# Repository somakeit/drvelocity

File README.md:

DrVelocity
==========

A ti DRV8704 based high power dual DC brushed motor controller with Atmel 328 MCU (Arduino Uno) onboard.

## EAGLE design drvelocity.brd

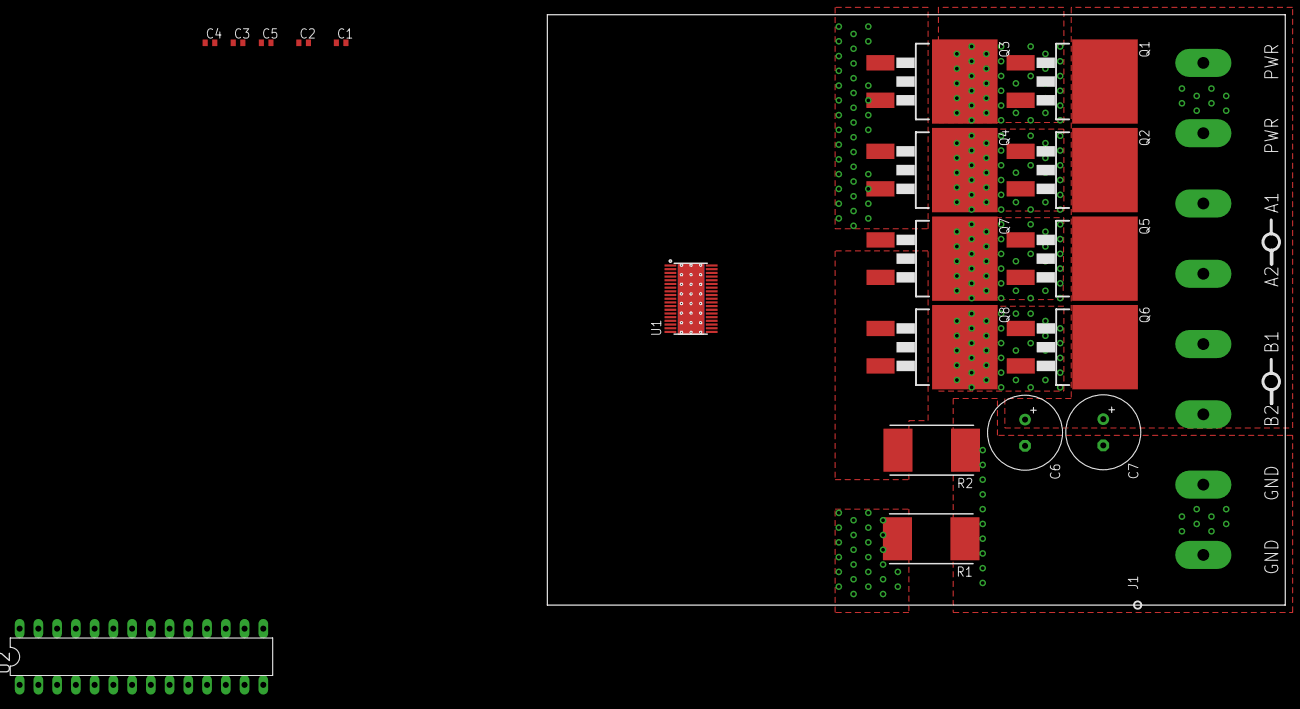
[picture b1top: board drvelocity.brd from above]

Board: 2 copper layers, 100.0 x 80.0 mm, 20 parts (0 on the bottom side), 21 nets, no tracks yet.

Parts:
C1, C2, C5: 0.1; C0402
C3, C4: 1; C0402
C6, C7: 100; E3,5-10
J1: MOLEX_BARRIER_8
Q1, Q2, Q3, Q4, Q5, Q6, Q7, Q8: IRF3704S; D2PACK
R1, R2: 1m; R4527
U1: DRV8704; HTSSOP-38
U2: ATMEGA168-20P; DIL28-3

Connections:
A1HS: Q1.1, U1.36
A1LS: Q3.1, U1.35
A2HS: Q2.1, U1.31
A2LS: Q4.1, U1.32
AISENP: Q3.3, Q4.3, R1.2, U1.34
AOUT1: J1.6, Q1.3, Q3.2, U1.37
AOUT2: J1.5, Q2.3, Q4.2, U1.30
B1HS: Q5.1, U1.27
B1LS: Q7.1, U1.26
B2HS: Q6.1, U1.22
B2LS: Q8.1, U1.23
BISENP: Q7.3, Q8.3, R2.2, U1.25
BOUT1: J1.4, Q5.3, Q7.2, U1.28
BOUT2: J1.3, Q6.3, Q8.2, U1.21
GND: C2.1, C3.1, C4.1, C5.1, C6.-, C7.-, J1.1, J1.2, R1.1, R2.1, U1.5, U1.19, U1.24, U1.29, U1.33, U1.38, U1.PPAD
unnamed: C1.2, U1.1
unnamed: C1.1, U1.2
V5: C2.2, U1.6
VCP: C3.2, U1.3
VINT: C4.2, U1.7
VM: C5.2, C6.+, C7.+, J1.7, J1.8, Q1.2, Q2.2, Q5.2, Q6.2, U1.4

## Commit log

2016-03-30 DRV8704 part complete & start of schematic
2016-03-30 Freakin lawyers man!
2016-04-02 Lay out H-Bridge
